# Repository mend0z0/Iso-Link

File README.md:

## Latest update

The layout is done, working on documentation and getting prepared for PCBA.

# Project

&nbsp;&nbsp;&nbsp;&nbsp;&nbsp;&nbsp;&nbsp;Iso-Link is a full-featured gateway that provides access to multiple industrial/automotive ports such as RS485, CAN, LIN, and DALI through 2.4GHz Wi-Fi (ESP32-S3) or Wi-Fi 6 (Stalwart Module). This gateway comes with APIs to facilitate the communication on popular industrial/automative protocols for troubleshooting the line, monitoring, and controlling connected devices to each bus line. In addition, developing a new system based on this gateway will make the development time faster and more reliable. Here is a list of protocols that will be supported by this device.

|RS485|CANBus|DALI|LIN|I2C|
|:---|:---|:---|:---|:---|
|1. Modbus ASCII<br>2. Modbus RTU <br>3. Modbus-TCP<br>4. Profibus DP <br>5. DNP3 <br>6. BACnet MS/TP<br>7. HART<br>8. IEC 61850<br>9. IEC 62056|1. CANOpen<br>2. J1939<br>3. DeviceNet<br>4. NMEA 2000<br>5. SAE J1708<br>6. OBD-II <br>7. CANopen Safety<br>8. FlexRay<br>9. ISO 11898-1|1. DALI-2<br>2. DALI-2/DT8<br>3. DALI-2/DT6<br>4. DALI+<br>5. BACnet<br>6. KNX|1. SAE J2602 <br>2. UDS on LIN<br>3. BWM LIN Protocol|1. I2C<br>2. SMBus<br>3. PMBus|

## Category

__IOT, Development Board__

## Features

- Isolated & SVP Ports
- 1 x USB2.0 OTG Port
- Single Power Supply (+6V ~ +36V)
- Integration of AI or LM machines to control and analyze your system.
- Digitalized Impedance Terminator

## System Design Block Diagram

## Hardware System Design Block Diagram

## Firmware System Design Block Diagram

## WBS Block Diagram

## Technology

|Specification|
|:---|
|<table><tbody><tr><td colspan="2" align="center">__Hardware__</h4></td></tr><tr><td>__Microchip :__</td> <td> Std.: ESP32-S3 / Prem.: STM32U5 </td></tr> <tr><td>__PCB Layers :__</td> <td> 4 Layers </td></tr> <tr><td>__Board Dimensions :__ </td> <td> 75 x 50 mm </td></tr> <tr><td>__CAD :__</td> <td> KiCAD </td></tr><tr><td colspan="2" align="center">__Firmware__</h4></td></tr><tr><td>__Language :__</td> <td> C </td></tr> <tr><td>__OS :__</td> <td> FreeRTOS </td></tr> <tr><td>__IDE :__</td> <td> Espressif-IDE / STM32CubeIDE </td></tr><tr><td colspan="2" align="center">__Application__</h4></td></tr><tr><td>__Language :__</td> <td> Python </td></tr> <tr><td>__App Type :__</td> <td> Web Application </td></tr> <tr><td>__IDE :__</td> <td> VSC </td></tr></table>|

|PCB Top View|PCB Bottom View|
|:---:|:---:|
|||

|Final Device Top|Final Device Bottom|
|:---:|:---:|
|||

## Videos

[Update On The Project](https://www.youtube.com/watch?v=Y3GoYqw6YXA&list=PLBWrS0_J_mZ2AYpXI1URpqJv-m0bLa1Cb)

## Author

- [@Siavash Taher Parvar](https://www.linkedin.com/in/mend0z0)

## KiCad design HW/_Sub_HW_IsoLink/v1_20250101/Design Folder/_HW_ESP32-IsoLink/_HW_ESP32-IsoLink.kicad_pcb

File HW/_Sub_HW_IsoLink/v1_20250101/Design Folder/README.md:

# TODO list

A brief description of this todo list belongs to what project

## Tasks

- #### MUST to DO (List the works that proper working of project depends on these tasks):
    - Replace the terminal blocks with 01x14 Pheonix 5.08mm
    - Add the board size
    - Add better SVP protection and some PTC on the line
	- Add terminator Resistor spot (It can be only 2 pins that a screw resistor will be placed on the enclosure.
	- Connect the connectors shield to the gnd via res and cap
	- Run USB diff pair properly and with respect to 50ohm impedance.
	- Adjust the size of PCB to be fit in a DIN rail box
	- Find a better Buck regulator.
	- 
	-
	- 
	- 
	- 
	- 
- #### Important (List the works that efficient and optimized functionality of project depends on these tasks):
    - 
    -
    - 
- #### General (List tasks that are good to be done but the functionality of project doesn't depend on these):
    - 
    -
    -

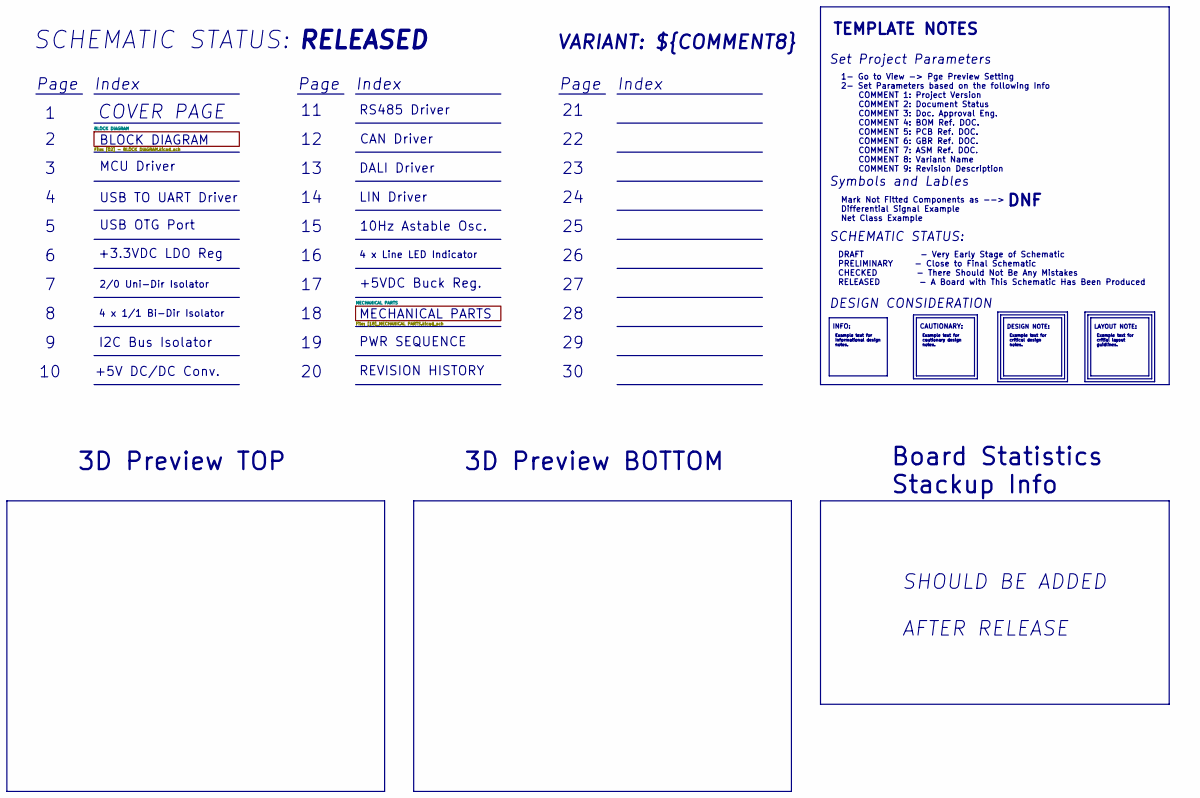
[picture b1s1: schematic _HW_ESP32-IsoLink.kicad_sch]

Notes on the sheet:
RS485 Driver
DALI Driver
DNF
REVISION HISTORY
Index
Symbols and Lables
Page
10Hz Astable Osc.
3D Preview BOTTOM
LIN Driver
SHOULD BE ADDED AFTER RELEASE
I2C Bus Isolator
Example text for cautionary design notes.
${ISSUE_DATE}
CAN Driver
INFO:
COVER PAGE
4 x 1/1 Bi-Dir Isolator
Example text for Informational design notes.
Example text for critical design notes.
SCHEMATIC STATUS:
DRAFT - Very Early Stage of Schematic PRELIMINARY - Close to Final Schematic CHECKED - There Should Not Be Any Mistakes RELEASED - A Board with This Schematic Has Been Produced
TEMPLATE NOTES
VARIANT: ${COMMENT8}
1- Go to View -> Pge Preview Setting 2- Set Parameters based on the following Info COMMENT 1: Project Version COMMENT 2: Document Status COMMENT 3: Doc. Approval Eng. COMMENT 4: BOM Ref. DOC. COMMENT 5: PCB Ref. DOC. COMMENT 6: GBR Ref. DOC. COMMENT 7: ASM Ref. DOC. COMMENT 8: Variant Name COMMENT 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
Mark Not Fitted Components as --> Differential Signal Example Net Class Example
MCU Driver
Set Project Parameters
SCHEMATIC STATUS:
Example text for critial layout guidlines.
+3.3VDC LDO Reg
${COMMENT2}
MECHANICAL PARTS
2/0 Uni-Dir Isolator
CAUTIONARY:
DESIGN CONSIDERATION
USB OTG Port
+5V DC/DC Conv.
USB TO UART Driver
3D Preview TOP

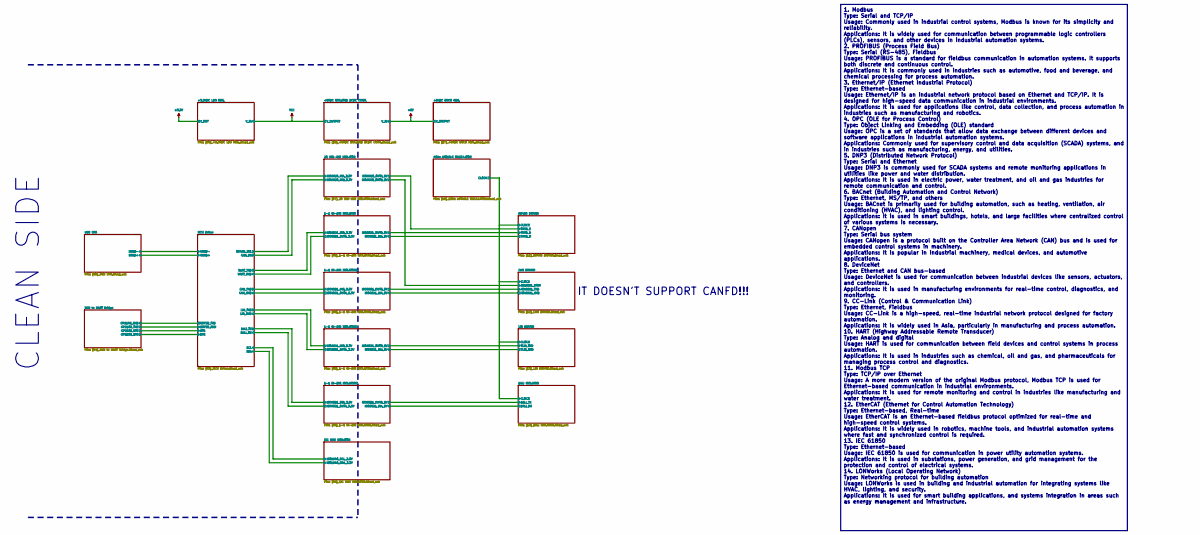
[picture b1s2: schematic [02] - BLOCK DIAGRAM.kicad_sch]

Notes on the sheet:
1. Modbus Type: Serial and TCP/IP Usage: Commonly used in industrial control systems, Modbus is known for its simplicity and reliability. Applications: It is widely used for communication between programmable logic controllers (PLCs), sensors, and other devices in industrial automation systems. 2. 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
IT DOESN'T SUPPORT CANFD!!!
CLEAN SIDE

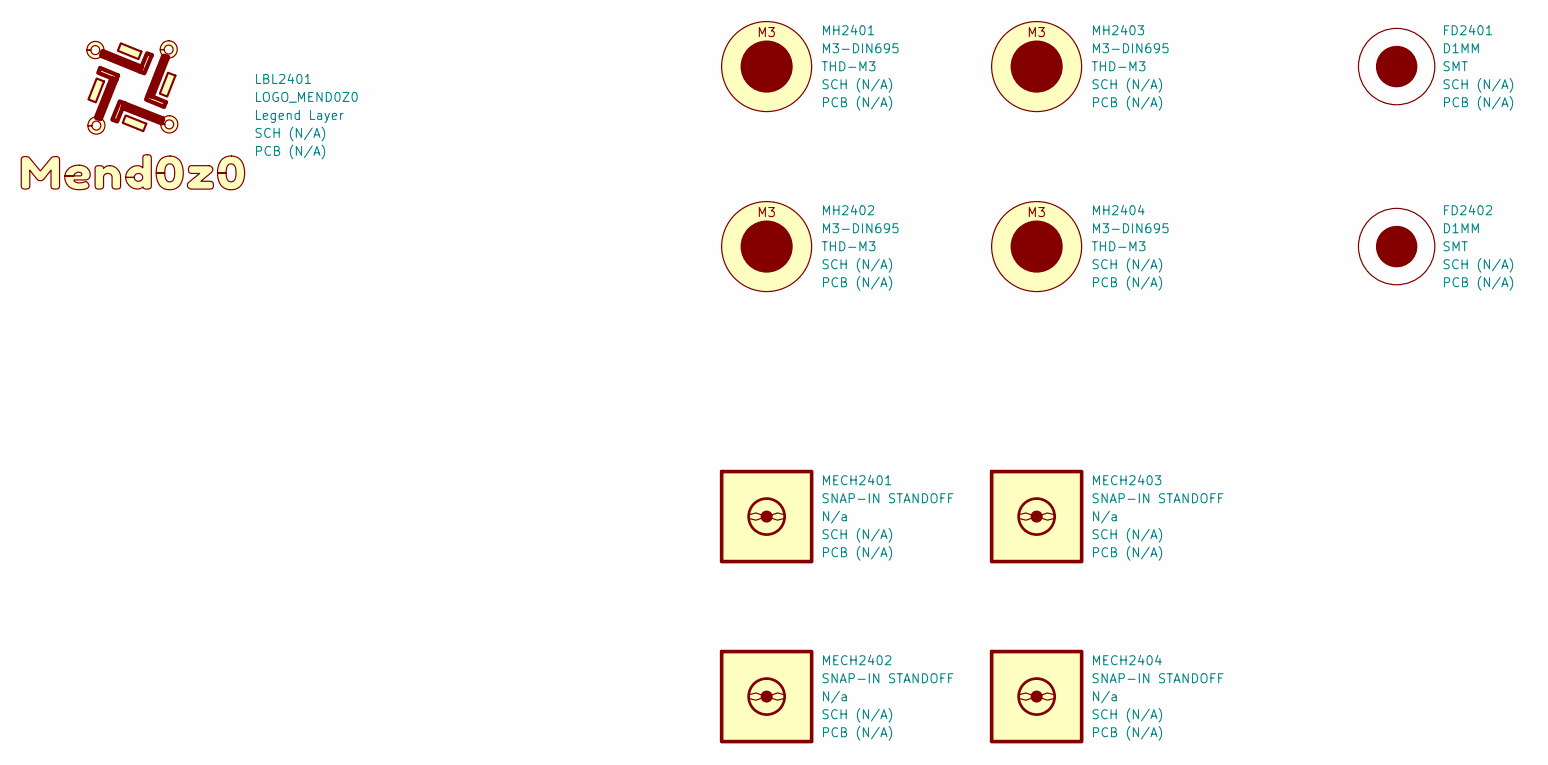
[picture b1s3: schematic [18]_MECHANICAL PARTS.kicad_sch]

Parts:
FD2401, FD2402: D1MM; Fiducial_1mm_Mask2mm; MPN 1 MPN 1
LBL2401: LOGO_MEND0Z0; Label_Logo_Mend0z0; MPN 1 MPN 1
MECH2401, MECH2402, MECH2403, MECH2404: SNAP-IN STANDOFF; Adhesive back Snap-in Standoff - M3; MPN 1 ‎pta230330tt0350
MH2401, MH2402, MH2403, MH2404: M3-DIN695; MountingHole_3.2mm_M3_DIN965; MPN 1 MPN 1

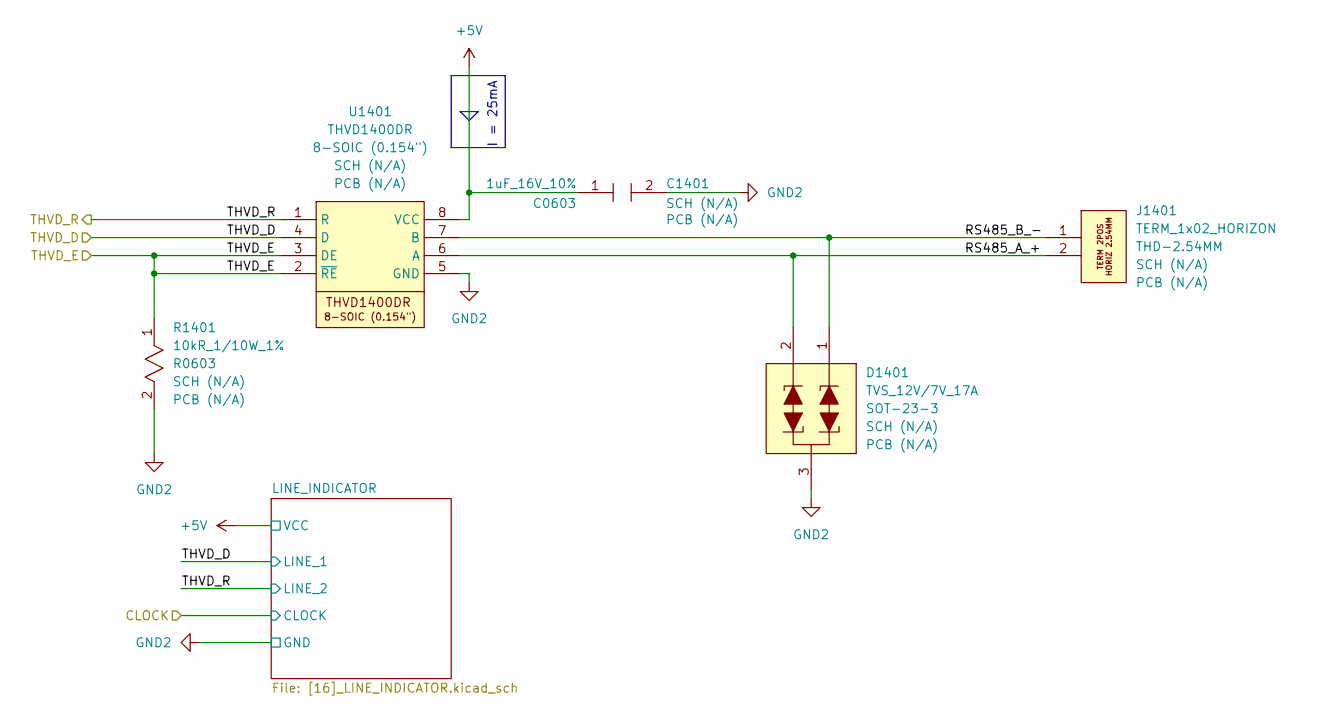
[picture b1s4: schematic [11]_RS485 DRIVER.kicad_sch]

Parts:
C1401: 1uF_16V_10%; C_0603_1608Metric; MPN 1 CL10B105KO8NNNC
D1401: TVS_12V/7V_17A; SOT-23-3; MPN 1 CDSOT23-SM712
J1401: TERM_1x02_HORIZON; TerminalBlock-2.54-2P_1x02_P2.54mm_Horizontal; MPN 1 691210910002
R1401: 10kR_1/10W_1%; R_0603_1608Metric; MPN 1 ERJ-3EKF1002V
U1401: THVD1400DR; SOIC-8_3.9x4.9mm_P1.27mm; MPN 1 THVD1400DR

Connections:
+5V: C1401.1, U1401.8 (VCC); also elsewhere on the board
/BLOCK DIAGRAM/1-1 BI-DIR ISOLATOR/ISO6521_INA: U1401.1 (R); also elsewhere on the board
/BLOCK DIAGRAM/1-1 BI-DIR ISOLATOR/ISO6521_OUTB: U1401.4 (D); also elsewhere on the board
/BLOCK DIAGRAM/20 UIN-DIR ISOLATOR/ISO6520_OUTA: R1401.1, U1401.2 (~RE), U1401.3 (DE); also elsewhere on the board
/BLOCK DIAGRAM/RS485 DRIVER/RS485_A_+: D1401.2, J1401.2, U1401.6 (A)
/BLOCK DIAGRAM/RS485 DRIVER/RS485_B_-: D1401.1, J1401.1, U1401.7 (B)
GND2: C1401.2, D1401.3, R1401.2, U1401.5 (GND); also elsewhere on the board

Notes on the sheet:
I = 25mA

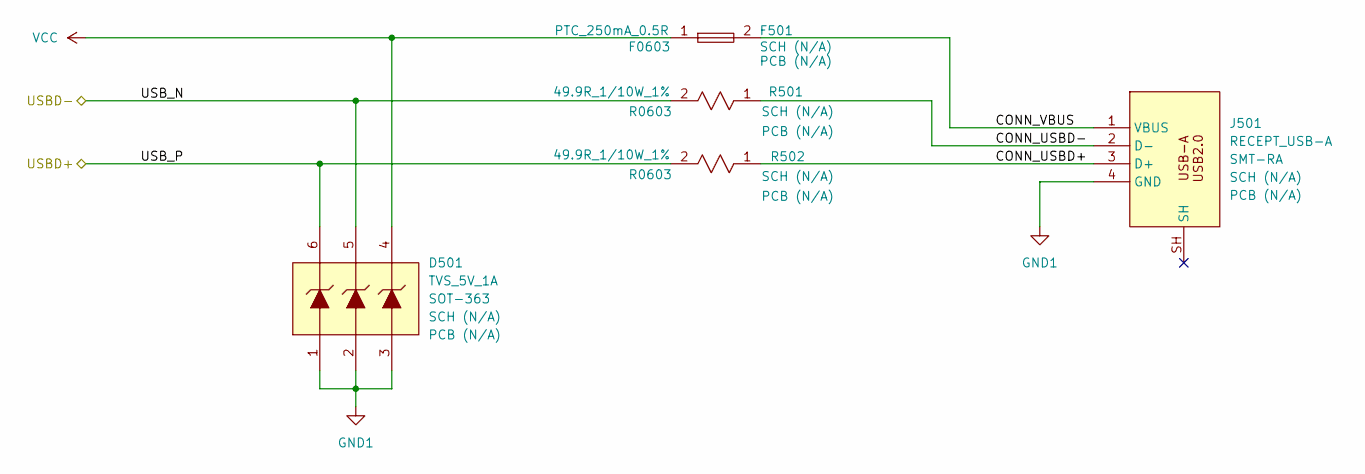
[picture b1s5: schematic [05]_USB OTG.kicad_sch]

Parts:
D501: TVS_5V_1A; SOT-363_SC-70-6; MPN 1 PE4105C3C6_R1_00001
F501: PTC_250mA_0.5R; Fuse_0603_1608Metric; MPN 1 SMD0603B025TF
J501: RECEPT_USB-A; USB TYPE-A 2.0 CONNECTOR, RIGHT, SMT; MPN 1 RAHUA20E
R501, R502: 49.9R_1/10W_1%; R_0603_1608Metric; MPN 1 RMCF0603FT49R9

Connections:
/BLOCK DIAGRAM/MCU Driver/ESP32_USBD+: D501.5, R501.2; also elsewhere on the board
/BLOCK DIAGRAM/MCU Driver/ESP32_USBD-: D501.6, R502.2; also elsewhere on the board
/BLOCK DIAGRAM/USB OTG/CONN_USBD+: J501.3 (D+), R502.1
/BLOCK DIAGRAM/USB OTG/CONN_USBD-: J501.2 (D-), R501.1
/BLOCK DIAGRAM/USB OTG/CONN_VBUS: F501.2, J501.1 (VBUS)
GND1: D501.1, D501.2, D501.3, J501.4 (GND); also elsewhere on the board
VCC: D501.4, F501.1; also elsewhere on the board

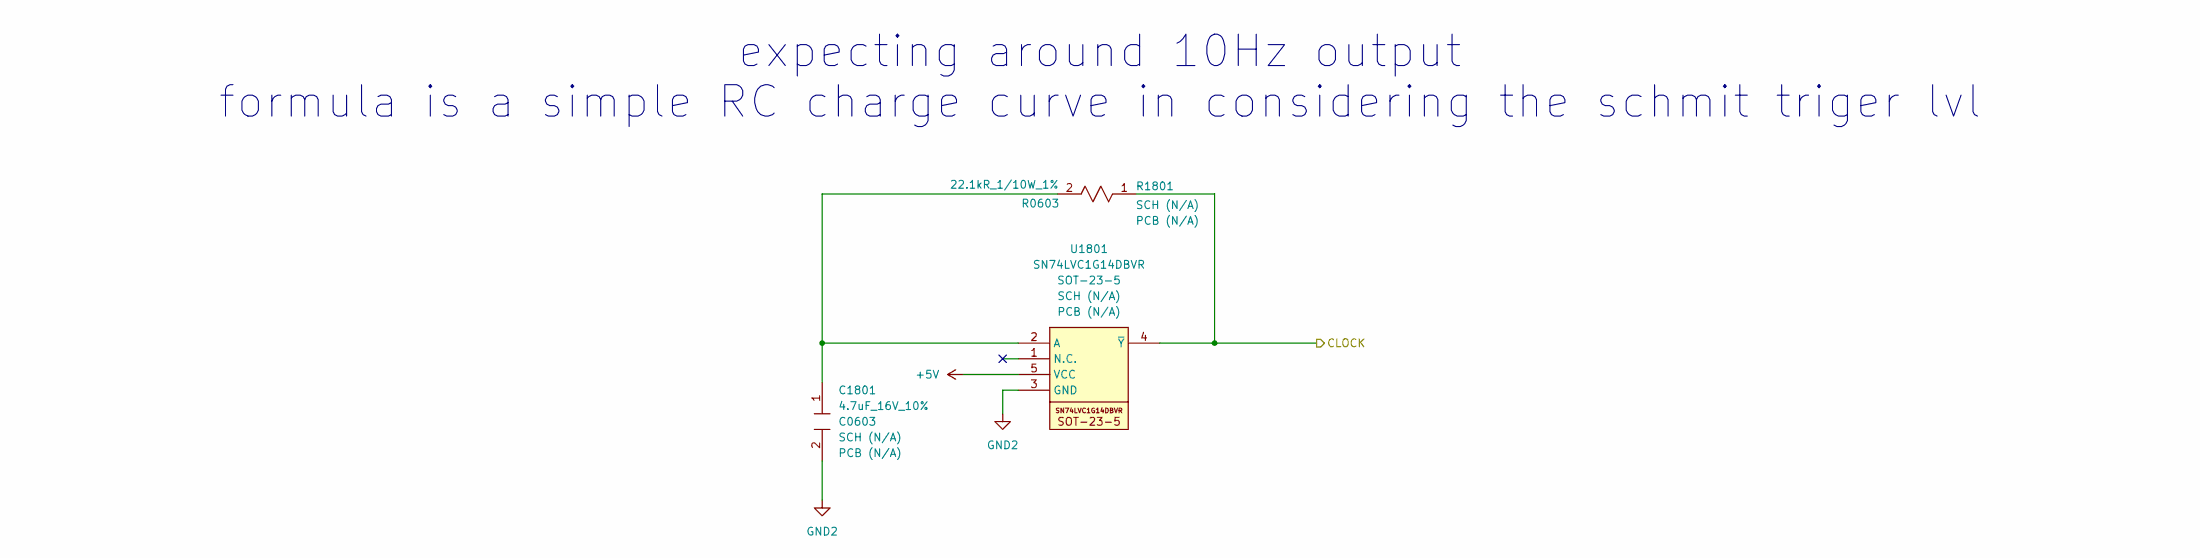
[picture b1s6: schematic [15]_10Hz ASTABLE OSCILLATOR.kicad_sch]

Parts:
C1801: 4.7uF_16V_10%; C_0603_1608Metric; MPN 1 CL10A475KO8NNNC
R1801: 22.1kR_1/10W_1%; R_0603_1608Metric; MPN 1 RMCF0603FT22K1
U1801: SN74LVC1G14DBVR; SOT-23-5; MPN 1 SN74LVC1G14DBVR

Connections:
+5V: U1801.5 (VCC); also elsewhere on the board
/BLOCK DIAGRAM/CAN DRIVER/LINE_INDICATOR1/CLOCK: R1801.1, U1801.4 (~Y); also elsewhere on the board
GND2: C1801.2, U1801.3 (GND); also elsewhere on the board
unnamed: C1801.1, R1801.2, U1801.2 (A)

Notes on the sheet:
expecting around 10Hz output formula is a simple RC charge curve in considering the schmit triger lvl

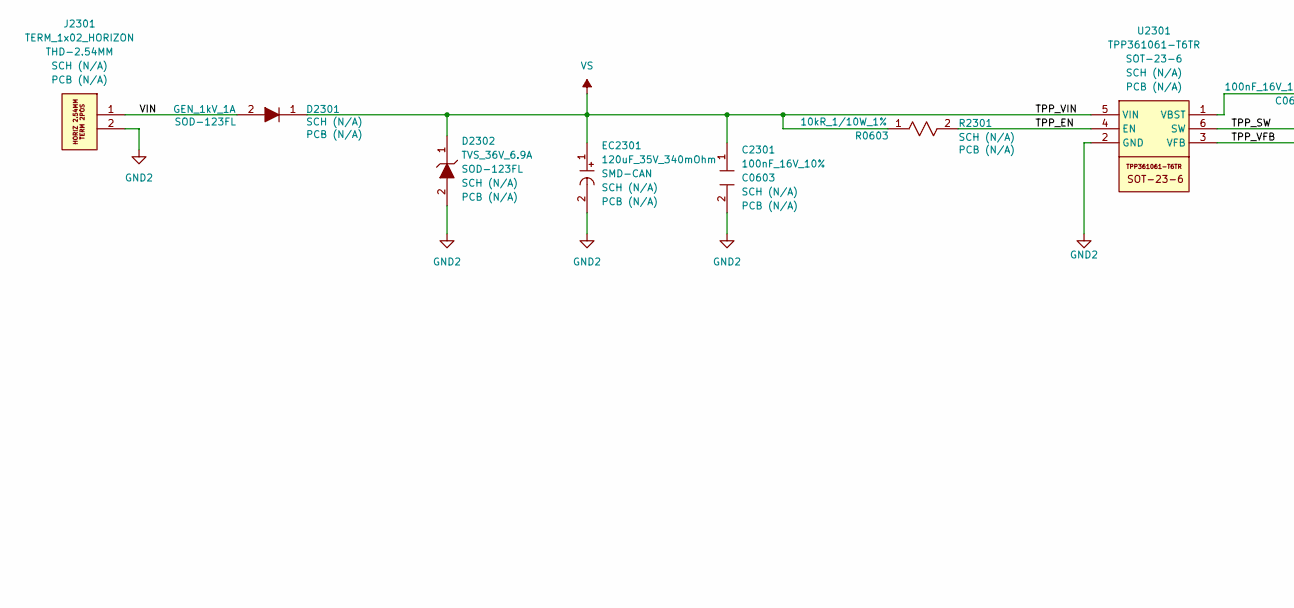
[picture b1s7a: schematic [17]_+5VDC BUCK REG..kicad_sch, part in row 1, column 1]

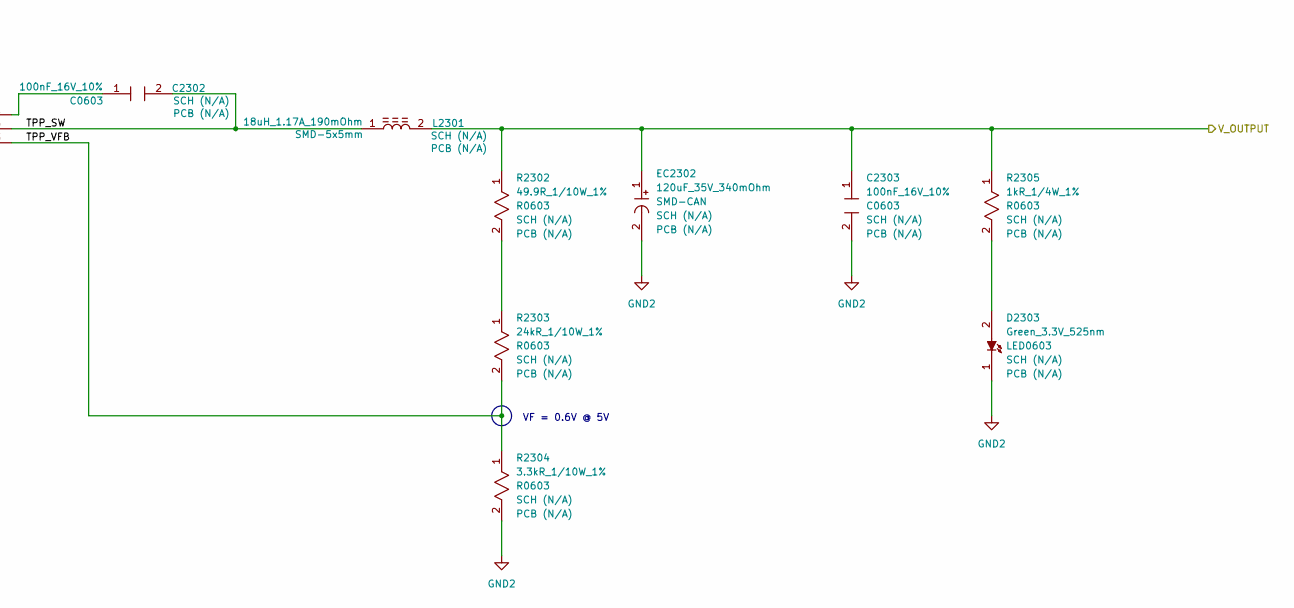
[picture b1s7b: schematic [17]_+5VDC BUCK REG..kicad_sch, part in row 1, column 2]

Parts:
C2301, C2302, C2303: 100nF_16V_10%; C_0603_1608Metric; MPN 1 CL10B104KO8NNNC
D2301: GEN_1kV_1A; D_SOD-123F; MPN 1 SL1M
D2302: TVS_36V_6.9A; D_SOD-123F; MPN 1 TPSMF4L36A
D2303: Green_3.3V_525nm; LED_0603_1608Metric; MPN 1 B1911NG--20D000214U1930
EC2301, EC2302: 120uF_35V_340mOhm; CAP_Elec_6.30mm Dia x 6.60mm L x 6.60mm W; MPN 1 EEE-FNV121XUP
J2301: TERM_1x02_HORIZON; TerminalBlock-2.54-2P_1x02_P2.54mm_Horizontal; MPN 1 691210910002
L2301: 18uH_1.17A_190mOhm; IND_SRN5020; MPN 1 SRN5020TA-180M
R2301: 10kR_1/10W_1%; R_0603_1608Metric; MPN 1 ERJ-3EKF1002V
R2302: 49.9R_1/10W_1%; R_0603_1608Metric; MPN 1 RMCF0603FT49R9
R2303: 24kR_1/10W_1%; R_0603_1608Metric; MPN 1 RMCF0603FG24K0
R2304: 3.3kR_1/10W_1%; R_0603_1608Metric; MPN 1 RMCF0603FT3K30
R2305: 1kR_1/4W_1%; R_0603_1608Metric; MPN 1 RCS06031K00FKEA
U2301: TPP361061-T6TR; SOT-23-6; MPN 1 TPP361061-T6TR

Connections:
+5V: C2303.1, EC2302.1, L2301.2, R2302.1, R2305.1; also elsewhere on the board
/BLOCK DIAGRAM/+5VDC BUCK REG./TPP_EN: R2301.2, U2301.4 (EN)
/BLOCK DIAGRAM/+5VDC BUCK REG./TPP_SW: C2302.2, L2301.1, U2301.6 (SW)
/BLOCK DIAGRAM/+5VDC BUCK REG./TPP_VFB: R2303.2, R2304.1, U2301.3 (VFB)
/BLOCK DIAGRAM/+5VDC BUCK REG./VIN: D2301.2, J2301.1
GND2: C2301.2, C2303.2, D2302.2, D2303.1, EC2301.2, EC2302.2, J2301.2, R2304.2, U2301.2 (GND); also elsewhere on the board
unnamed: D2303.2, R2305.2
unnamed: R2302.2, R2303.1
unnamed: C2302.1, U2301.1 (VBST)
VS: C2301.1, D2301.1, D2302.1, EC2301.1, R2301.1, U2301.5 (VIN); also elsewhere on the board

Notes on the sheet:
VF = 0.6V @ 5V

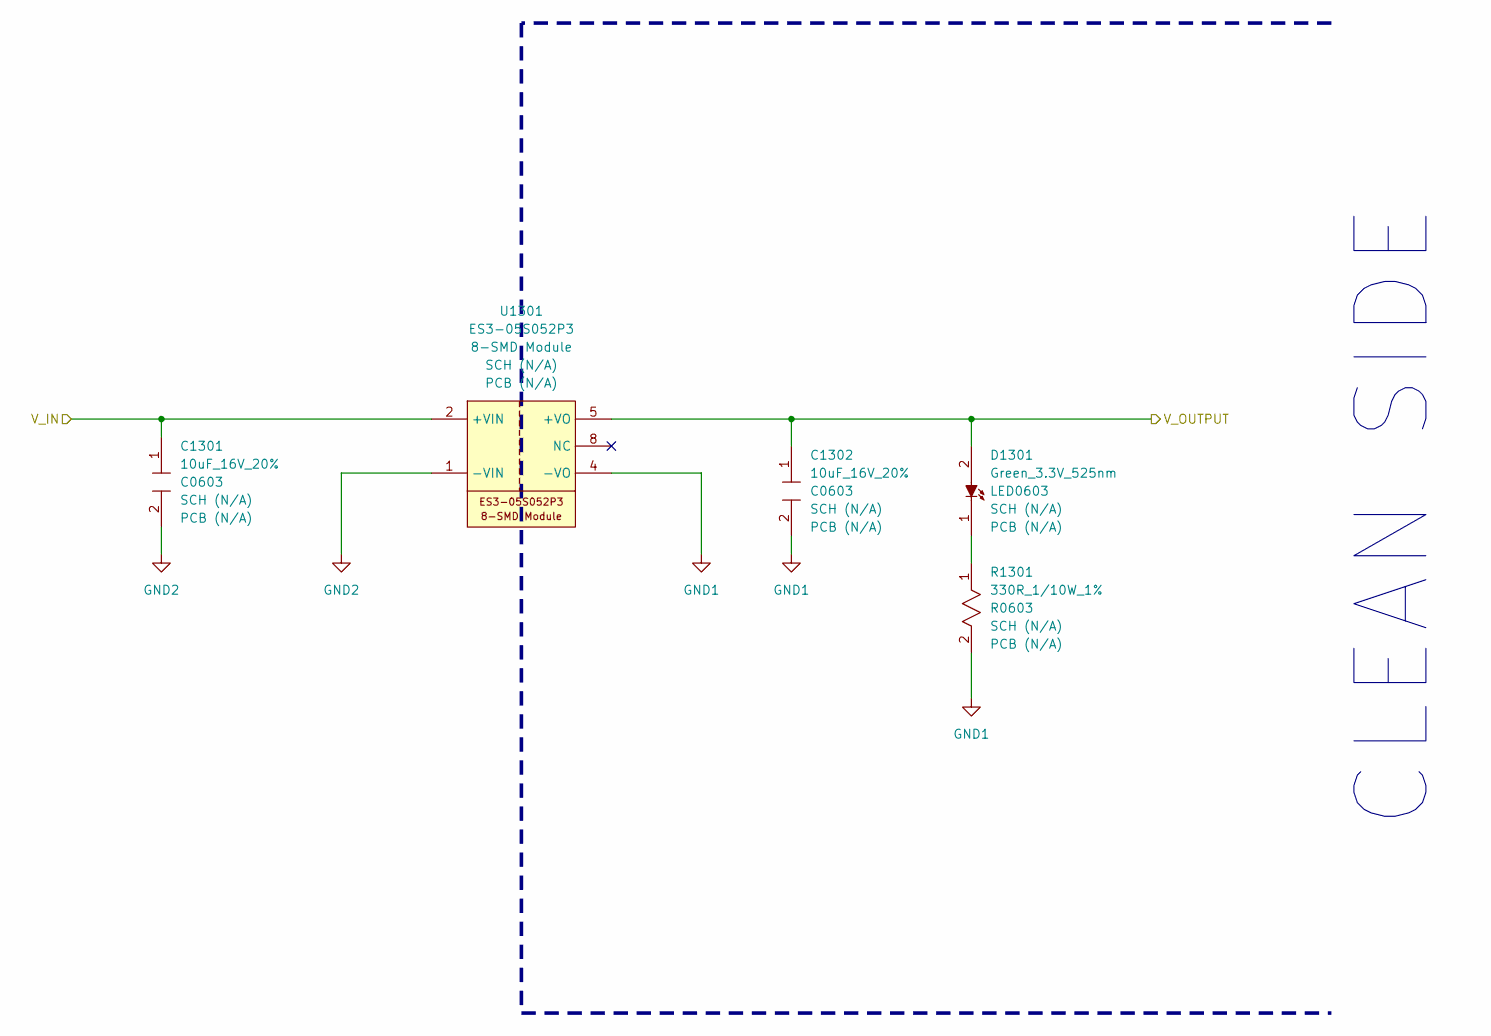
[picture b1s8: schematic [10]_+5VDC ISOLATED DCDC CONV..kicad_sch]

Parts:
C1301, C1302: 10uF_16V_20%; C_0603_1608Metric; MPN 1 CL10X106MO8NRNC
D1301: Green_3.3V_525nm; LED_0603_1608Metric; MPN 1 B1911NG--20D000214U1930
R1301: 330R_1/10W_1%; R_0603_1608Metric; MPN 1 CRG0603F330R
U1301: ES3-05S052P3; 8-SMD Module, 5 Leads; MPN 1 ES3-05S052P3

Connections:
+5V: C1301.1, U1301.2 (+VIN); also elsewhere on the board
GND1: C1302.2, R1301.2, U1301.4 (-VO); also elsewhere on the board
GND2: C1301.2, U1301.1 (-VIN); also elsewhere on the board
unnamed: D1301.1, R1301.1
VCC: C1302.1, D1301.2, U1301.5 (+VO); also elsewhere on the board

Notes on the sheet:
CLEAN SIDE

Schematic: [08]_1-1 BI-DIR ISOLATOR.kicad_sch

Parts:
C801, C802: 1uF_16V_10%; C_0603_1608Metric; MPN 1 CL10B105KO8NNNC
U801: ISO6521DR; SOIC-8_3.9x4.9mm_P1.27mm; MPN 1 ISO6521DR

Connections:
+3.3V: C801.1, U801.1 (VCC1); also elsewhere on the board
+5V: C802.1, U801.8 (VCC2); also elsewhere on the board
/BLOCK DIAGRAM/1-1 BI-DIR ISOLATOR/ISO6521_INA: U801.7 (INA); also elsewhere on the board
/BLOCK DIAGRAM/1-1 BI-DIR ISOLATOR/ISO6521_INB: U801.3 (INB); also elsewhere on the board
/BLOCK DIAGRAM/1-1 BI-DIR ISOLATOR/ISO6521_OUTA: U801.2 (OUTA); also elsewhere on the board
/BLOCK DIAGRAM/1-1 BI-DIR ISOLATOR/ISO6521_OUTB: U801.6 (OUTB); also elsewhere on the board
GND1: C801.2, U801.4 (GND1); also elsewhere on the board
GND2: C802.2, U801.5 (GND2); also elsewhere on the board

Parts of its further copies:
C901, C902, C1001, C1002, C1101, C1102: 1uF_16V_10%; C_0603_1608Metric; MPN 1 CL10B105KO8NNNC
U901, U1001, U1101: ISO6521DR; SOIC-8_3.9x4.9mm_P1.27mm; MPN 1 ISO6521DR

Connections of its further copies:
+3.3V: C901.1, C1001.1, C1101.1, U901.1 (VCC1), U1001.1 (VCC1), U1101.1 (VCC1); also elsewhere on the board
+5V: C902.1, C1002.1, C1102.1, U901.8 (VCC2), U1001.8 (VCC2), U1101.8 (VCC2); also elsewhere on the board
/BLOCK DIAGRAM/1-1 BI-DIR ISOLATOR1/ISO6521_INA: U901.7 (INA); also elsewhere on the board
/BLOCK DIAGRAM/1-1 BI-DIR ISOLATOR1/ISO6521_INB: U901.3 (INB); also elsewhere on the board
/BLOCK DIAGRAM/1-1 BI-DIR ISOLATOR1/ISO6521_OUTA: U901.2 (OUTA); also elsewhere on the board
/BLOCK DIAGRAM/1-1 BI-DIR ISOLATOR1/ISO6521_OUTB: U901.6 (OUTB); also elsewhere on the board
/BLOCK DIAGRAM/1-1 BI-DIR ISOLATOR2/ISO6521_INA: U1001.7 (INA); also elsewhere on the board
/BLOCK DIAGRAM/1-1 BI-DIR ISOLATOR2/ISO6521_INB: U1001.3 (INB); also elsewhere on the board
/BLOCK DIAGRAM/1-1 BI-DIR ISOLATOR2/ISO6521_OUTA: U1001.2 (OUTA); also elsewhere on the board
/BLOCK DIAGRAM/1-1 BI-DIR ISOLATOR2/ISO6521_OUTB: U1001.6 (OUTB); also elsewhere on the board
/BLOCK DIAGRAM/1-1 BI-DIR ISOLATOR3/ISO6521_INA: U1101.7 (INA); also elsewhere on the board
/BLOCK DIAGRAM/1-1 BI-DIR ISOLATOR3/ISO6521_INB: U1101.3 (INB); also elsewhere on the board
/BLOCK DIAGRAM/1-1 BI-DIR ISOLATOR3/ISO6521_OUTA: U1101.2 (OUTA); also elsewhere on the board
/BLOCK DIAGRAM/1-1 BI-DIR ISOLATOR3/ISO6521_OUTB: U1101.6 (OUTB); also elsewhere on the board
GND1: C901.2, C1001.2, C1101.2, U901.4 (GND1), U1001.4 (GND1), U1101.4 (GND1); also elsewhere on the board
GND2: C902.2, C1002.2, C1102.2, U901.5 (GND2), U1001.5 (GND2), U1101.5 (GND2); also elsewhere on the board

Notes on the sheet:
I = 15mA

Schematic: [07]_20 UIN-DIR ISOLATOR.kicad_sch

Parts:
C701, C702: 1uF_16V_10%; C_0603_1608Metric; MPN 1 CL10B105KO8NNNC
U701: ISO6520DR; SOIC-8_3.9x4.9mm_P1.27mm; MPN 1 ISO6520DR

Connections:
+3.3V: C701.1, U701.1 (VCC1); also elsewhere on the board
+5V: C702.1, U701.8 (VCC2); also elsewhere on the board
/BLOCK DIAGRAM/20 UIN-DIR ISOLATOR/ISO6520_INA: U701.2 (INA); also elsewhere on the board
/BLOCK DIAGRAM/20 UIN-DIR ISOLATOR/ISO6520_INB: U701.3 (INB); also elsewhere on the board
/BLOCK DIAGRAM/20 UIN-DIR ISOLATOR/ISO6520_OUTA: U701.7 (OUTA); also elsewhere on the board
/BLOCK DIAGRAM/20 UIN-DIR ISOLATOR/ISO6520_OUTB: U701.6 (OUTB); also elsewhere on the board
GND1: C701.2, U701.4 (GND1); also elsewhere on the board
GND2: C702.2, U701.5 (GND2); also elsewhere on the board

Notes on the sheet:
I = 15mA

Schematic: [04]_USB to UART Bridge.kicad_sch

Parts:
C401: 4.7uF_16V_10%; C_0603_1608Metric; MPN 1 CL10A475KO8NNNC
C402: 100nF_16V_10%; C_0603_1608Metric; MPN 1 CL10B104KO8NNNC
C403: 1uF_16V_10%; C_0603_1608Metric; MPN 1 CL10B105KO8NNNC
D401: TVS_5V_1A; SOT-363_SC-70-6; MPN 1 PE4105C3C6_R1_00001
D402: GEN_1kV_1A; D_SOD-123F; MPN 1 SL1M
D403: Blue_3.3V_470nm; LED_0603_1608Metric; MPN 1 B1931NB--20C007614U1930
D404: Orange_2V_605nm; LED_0603_1608Metric; MPN 1 B1911UD--20D001014U1930
F401: PTC_250mA_0.5R; Fuse_0603_1608Metric; MPN 1 SMD0603B025TF
J401: micro-B USB; USB_Micro-B_Amphenol_10118194_Horizontal; MPN 1 10118194-0001LF
R401, R402: 49.9R_1/10W_1%; R_0603_1608Metric; MPN 1 RMCF0603FT49R9
R403: 22.1kR_1/10W_1%; R_0603_1608Metric; MPN 1 RMCF0603FT22K1
R404: 47.5kR_1/10W_1%; R_0603_1608Metric; MPN 1 RMCF0603FT47K5
R405: 4.7kR_1/10W_1%; R_0603_1608Metric; MPN 1 ERJ-3EKF4701V
R406: 330R_1/10W_1%; R_0603_1608Metric; MPN 1 CRG0603F330R
U401: CP2102; QFN-24-1EP_4x4mm_P0.5mm_EP2.75x2.75mm_ThermalVias; MPN 1 CP2102N-A02-GQFN24

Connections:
+3.3V: C401.1, C402.1, C403.1, R405.1, R406.1, U401.5 (VIO), U401.6 (VDD), U401.7 (REGIN); also elsewhere on the board
/BLOCK DIAGRAM/MCU Driver/DTR: U401.23 (DTR); also elsewhere on the board
/BLOCK DIAGRAM/MCU Driver/ESP32_RXD0: U401.21 (TXD); also elsewhere on the board
/BLOCK DIAGRAM/MCU Driver/ESP32_TXD0: U401.20 (RXD); also elsewhere on the board
/BLOCK DIAGRAM/MCU Driver/RTS: U401.19 (RTS); also elsewhere on the board
/BLOCK DIAGRAM/USB to UART Bridge/CP2105_D+: D401.6, R402.2, U401.3 (D+)
/BLOCK DIAGRAM/USB to UART Bridge/CP2105_D-: D401.5, R401.2, U401.4 (D-)
/BLOCK DIAGRAM/USB to UART Bridge/CP2105_TGL_RX: D404.1, U401.13 (GPIO.1/RXT)
/BLOCK DIAGRAM/USB to UART Bridge/CP2105_TGL_TX: D403.1, U401.14 (GPIO.0/TXT)
/BLOCK DIAGRAM/USB to UART Bridge/CP2105_VBUS: R403.2, R404.1, U401.8 (VBUS)
/BLOCK DIAGRAM/USB to UART Bridge/CP2105_~RST: R405.2, U401.9 (~RST)
GND1: C401.2, C402.2, C403.2, D401.1, D401.2, D401.3, J401.5 (GND), R404.2, U401.2 (GND), U401.25 (GND); also elsewhere on the board
unnamed: D401.4, D402.2, F401.2
unnamed: D403.2, D404.2, R406.2
unnamed: J401.3 (D+), R402.1
unnamed: J401.2 (D-), R401.1
unnamed: F401.1, J401.1 (VBUS)
VCC: D402.1, R403.1; also elsewhere on the board

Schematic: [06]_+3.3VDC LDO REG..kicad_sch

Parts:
C601, C603: 10uF_16V_20%; C_0603_1608Metric; MPN 1 CL10X106MO8NRNC
C602: 1uF_16V_10%; C_0603_1608Metric; MPN 1 CL10B105KO8NNNC
R601: 4.7kR_1/10W_1%; R_0603_1608Metric; MPN 1 ERJ-3EKF4701V
SW601: SPST-NO_12V_0.05A; SW_Tactile_SPST_NO_Straight_CK_PTS636Sx25SMTRLFS; MPN 1 PTS636 SL50 SMTR LFS
U601: TLV75533PDBVR; SOT-23-5; MPN 1 TLV75533PDBVR

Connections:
+3.3V: C603.1, U601.5 (OUT); also elsewhere on the board
/BLOCK DIAGRAM/+3.3VDC LDO REG./TLV_RST: C602.1, R601.2, SW601.1, U601.3 (EN)
GND1: C601.2, C602.2, C603.2, SW601.2, U601.2 (GND); also elsewhere on the board
VCC: C601.1, R601.1, U601.1 (IN); also elsewhere on the board

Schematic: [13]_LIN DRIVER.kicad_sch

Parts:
C1601: 1uF_100V_10%; C_0603_1608Metric; MPN 1 GRM188D72A105ME01W
C1602: 220pF_100V_10%; C_0603_1608Metric; MPN 1 C0603C221K1RACTU
D1601: TVS_22V_1A; SOT-323_SC-70; MPN 1 MMBZ27VCWT3G
J1601: TERM_1x02_HORIZON; TerminalBlock-2.54-2P_1x02_P2.54mm_Horizontal; MPN 1 691210910002
R1601, R1603: 10kR_1/10W_1%; R_0603_1608Metric; MPN 1 ERJ-3EKF1002V
R1602: 24kR_1/10W_1%; R_0603_1608Metric; MPN 1 RMCF0603FG24K0
R1604: 1kR_1/4W_1%; R_0603_1608Metric; MPN 1 RCS06031K00FKEA
U1601: TLIN1021ADRQ1; SOIC-8_3.9x4.9mm_P1.27mm; MPN 1 TLIN1021ADRQ1

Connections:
+5V: R1601.1, R1603.1; also elsewhere on the board
/BLOCK DIAGRAM/1-1 BI-DIR ISOLATOR2/ISO6521_INA: R1601.2, U1601.1 (RXD); also elsewhere on the board
/BLOCK DIAGRAM/1-1 BI-DIR ISOLATOR2/ISO6521_OUTB: U1601.4 (TXD); also elsewhere on the board
GND2: C1601.2, C1602.2, D1601.2, J1601.2, U1601.5 (GND); also elsewhere on the board
unnamed: D1601.1, R1604.2
unnamed: R1603.2, U1601.2 (EN)
unnamed: C1602.1, D1601.3, J1601.1, U1601.6 (LIN)
unnamed: R1602.2, U1601.3 (WAKE)
VS: C1601.1, R1602.1, R1604.1, U1601.7 (VSUP); also elsewhere on the board

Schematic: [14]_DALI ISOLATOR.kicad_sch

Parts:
J1701: TERM_1x02_HORIZON; TerminalBlock-2.54-2P_1x02_P2.54mm_Horizontal; MPN 1 691210910002
Q1701: Z0103NN0,135; SOT-223; MPN 1 Z0103NN0,135
R1701: 47.5kR_1/10W_1%; R_0603_1608Metric; MPN 1 RMCF0603FT47K5
R1702: 47.5kR_1/10W_1%; R_0603_1608Metric; MPN 1 RMCF0603FT47K5; not fitted
U1701: LM358BIDR; SOIC-8_3.9x4.9mm_P1.27mm; MPN 1 LM358BIDR

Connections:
+5V: U1701.8 (V+); also elsewhere on the board
/BLOCK DIAGRAM/1-1 BI-DIR ISOLATOR3/ISO6521_INA: U1701.7 (OUT2); also elsewhere on the board
/BLOCK DIAGRAM/1-1 BI-DIR ISOLATOR3/ISO6521_OUTB: Q1701.3, R1701.1; also elsewhere on the board
/BLOCK DIAGRAM/DALI ISOLATOR/DALI+: J1701.1, Q1701.2, U1701.5 (IN2+)
/BLOCK DIAGRAM/DALI ISOLATOR/DALI-: J1701.2, Q1701.1, R1702.1, U1701.6 (IN2-)
GND2: R1701.2, R1702.2, U1701.4 (V-); also elsewhere on the board

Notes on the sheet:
THIS IS FOR TEST RIGHT NOW IF we had to give it a different potential
Voltage rating (IEC60929) In general, the interface voltage is high if there is no communication (idle state). The slopes of the received and transmitted data signal shall be 10 μs ≤ tfall ≤ 100 μs and 10 μs ≤ trise ≤ 100 μs at the ballast terminals of the digital interface. The voltage range shall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
Current rating (IEC60929) In non-active state, the sink current of the ballast shall not exceed 2 mA at ≤22,5 V because of the actual maximum number of ballasts per control unit. This shall be guaranteed by each ballast manufacturer. The ballast shall be able to sink at least 250 mA at ≤ 4,5 V at a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
DALI SPEC.
IEC60929 • Short specification – Maximum 64 individual addressable ballasts within one system – The ballast can not act as a master controller – Multiple ballast groups - Bi-phase coding for error detection (see E.4.3.6, Pulse diagram) - Asynchronous start-stop transmission protocol - Low informati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

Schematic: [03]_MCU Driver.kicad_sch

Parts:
C301, C302, C305: 100nF_16V_10%; C_0603_1608Metric; MPN 1 CL10B104KO8NNNC
C303, C304: 10uF_16V_20%; C_0603_1608Metric; MPN 1 CL10X106MO8NRNC
D301: Red_2V_631nm; LED_0603_1608Metric; MPN 1 B1931URO-20D000114U1930
Q301, Q302: BC847B-C; SOT-23-3; MPN 1 BC847B-C
R301, R302, R303, R305: 10kR_1/10W_1%; R_0603_1608Metric; MPN 1 ERJ-3EKF1002V
R304: 330R_1/10W_1%; R_0603_1608Metric; MPN 1 CRG0603F330R
SW301: SPST-NO_12V_0.05A; SW_Tactile_SPST_NO_Straight_CK_PTS636Sx25SMTRLFS; MPN 1 PTS636 SL50 SMTR LFS
U301: ESP32-S3; XCVR_ESP32-S3-WROOM-1-N4; MPN 1 ESP32-S3-WROOM-1-N4R2

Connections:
+3.3V: C303.1, C304.1, C305.1, R302.1, R304.1, R305.1, U301.2 (3V3); also elsewhere on the board
/BLOCK DIAGRAM/1-1 BI-DIR ISOLATOR1/ISO6521_INB: U301.4 (CAN-TXD_IO4); also elsewhere on the board
/BLOCK DIAGRAM/1-1 BI-DIR ISOLATOR1/ISO6521_OUTA: U301.5 (CAN-RXD_IO5); also elsewhere on the board
/BLOCK DIAGRAM/1-1 BI-DIR ISOLATOR2/ISO6521_INB: U301.33 (LIN-TX_IO40); also elsewhere on the board
/BLOCK DIAGRAM/1-1 BI-DIR ISOLATOR2/ISO6521_OUTA: U301.34 (LIN-RX_IO41); also elsewhere on the board
/BLOCK DIAGRAM/1-1 BI-DIR ISOLATOR3/ISO6521_INB: U301.31 (DALI-TX_IO38); also elsewhere on the board
/BLOCK DIAGRAM/1-1 BI-DIR ISOLATOR3/ISO6521_OUTA: U301.32 (DALI-RX_IO39); also elsewhere on the board
/BLOCK DIAGRAM/1-1 BI-DIR ISOLATOR/ISO6521_INB: U301.10 (U1TXD-IO17); also elsewhere on the board
/BLOCK DIAGRAM/1-1 BI-DIR ISOLATOR/ISO6521_OUTA: U301.11 (U1RXD-IO18); also elsewhere on the board
/BLOCK DIAGRAM/20 UIN-DIR ISOLATOR/ISO6520_INA: U301.12 (RS485-SEL_IO8); also elsewhere on the board
/BLOCK DIAGRAM/20 UIN-DIR ISOLATOR/ISO6520_INB: U301.6 (CAN-EN_IO6); also elsewhere on the board
/BLOCK DIAGRAM/I2C BUS ISOLATOR/ISO1640_SCL1: U301.7 (SDA_IO7); also elsewhere on the board
/BLOCK DIAGRAM/I2C BUS ISOLATOR/ISO1640_SDA1: U301.8 (SCL_IO15); also elsewhere on the board
/BLOCK DIAGRAM/MCU Driver/DTR: Q302.2, R301.1; also elsewhere on the board
/BLOCK DIAGRAM/MCU Driver/ESP32_EN: C301.1, Q301.3, R302.2, U301.3 (EN)
/BLOCK DIAGRAM/MCU Driver/ESP32_IO0: C302.1, Q302.3, R305.2, SW301.1, U301.27 (BOOT0_IO0)
/BLOCK DIAGRAM/MCU Driver/ESP32_RXD0: U301.36 (RXD0); also elsewhere on the board
/BLOCK DIAGRAM/MCU Driver/ESP32_TXD0: U301.37 (TXD0); also elsewhere on the board
/BLOCK DIAGRAM/MCU Driver/ESP32_USBD+: U301.13 (IO19_USB_D-); also elsewhere on the board
/BLOCK DIAGRAM/MCU Driver/ESP32_USBD-: U301.14 (IO20_USB_D+); also elsewhere on the board
/BLOCK DIAGRAM/MCU Driver/LED_IND: D301.1, U301.38 (LED-IND_IO2)
/BLOCK DIAGRAM/MCU Driver/RTS: Q301.2, R303.1; also elsewhere on the board
GND1: C301.2, C302.2, C303.2, C304.2, C305.2, SW301.2, U301.1 (GND), U301.40 (GND), U301.41 (GND); also elsewhere on the board
unnamed: D301.2, R304.2
unnamed: Q301.1, R301.2
unnamed: Q302.1, R303.2

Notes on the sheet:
https://docs.espressif.com/projects/esptool/en/latest/esp32/advanced-topics/boot-mode-selection.html
IO0
DTR
RTS
AUTO PROGRAMMING

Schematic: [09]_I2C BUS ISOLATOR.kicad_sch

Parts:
C1201, C1202: 1uF_16V_10%; C_0603_1608Metric; MPN 1 CL10B105KO8NNNC
J1201: TERM_1x03_HORIZON; TerminalBlock-2.54-3P_1x03_P2.54mm_Horizontal; MPN 1 691210910003
R1201, R1202: 4.7kR_1/10W_1%; R_0603_1608Metric; MPN 1 ERJ-3EKF4701V
R1203, R1204: 4.7kR_1/10W_1%; R_0603_1608Metric; MPN 1 ERJ-3EKF4701V; not fitted
U1201: ISO1640BDR; SOIC-8_3.9x4.9mm_P1.27mm; MPN 1 ISO1640BDR

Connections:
+3.3V: C1201.1, R1201.1, R1202.1, U1201.1 (VCC1); also elsewhere on the board
+5V: C1202.1, R1203.1, R1204.1, U1201.8 (VCC2); also elsewhere on the board
/BLOCK DIAGRAM/I2C BUS ISOLATOR/ISO1640_SCL1: R1201.2, U1201.3 (SCL1); also elsewhere on the board
/BLOCK DIAGRAM/I2C BUS ISOLATOR/ISO1640_SCL2: J1201.2, R1204.2, U1201.6 (SCL2)
/BLOCK DIAGRAM/I2C BUS ISOLATOR/ISO1640_SDA1: R1202.2, U1201.2 (SDA1); also elsewhere on the board
/BLOCK DIAGRAM/I2C BUS ISOLATOR/ISO1640_SDA2: J1201.1, R1203.2, U1201.7 (SDA2)
GND1: C1201.2, U1201.4 (GND1); also elsewhere on the board
GND2: C1202.2, J1201.3, U1201.5 (GND2); also elsewhere on the board

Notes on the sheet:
I = 15mA

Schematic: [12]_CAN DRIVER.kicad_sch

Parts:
C1501, C1502: 1uF_16V_10%; C_0603_1608Metric; MPN 1 CL10B105KO8NNNC
D1501: TVS_24V_3.5A; SOT-323_SC-70; MPN 1 PESD2IVN24-UX
J1501: TERM_1x02_HORIZON; TerminalBlock-2.54-2P_1x02_P2.54mm_Horizontal; MPN 1 691210910002
U1501: ATA6561-GAQW-N; SOIC-8_3.9x4.9mm_P1.27mm; MPN 1 ATA6561-GAQW-N

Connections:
+5V: C1501.1, C1502.1, U1501.3 (VCC), U1501.5 (VIO); also elsewhere on the board
/BLOCK DIAGRAM/1-1 BI-DIR ISOLATOR1/ISO6521_INA: U1501.4 (RXD); also elsewhere on the board
/BLOCK DIAGRAM/1-1 BI-DIR ISOLATOR1/ISO6521_OUTB: U1501.1 (TXD); also elsewhere on the board
/BLOCK DIAGRAM/20 UIN-DIR ISOLATOR/ISO6520_OUTB: U1501.8 (STBY); also elsewhere on the board
/BLOCK DIAGRAM/CAN DRIVER/ATA6561_CANH_+: D1501.1, J1501.1, U1501.7 (CANH)
/BLOCK DIAGRAM/CAN DRIVER/ATA6561_CANL_-: D1501.2, J1501.2, U1501.6 (CANL)
GND2: C1501.2, C1502.2, D1501.3, U1501.2 (GND); also elsewhere on the board

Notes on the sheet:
I = 70mA
